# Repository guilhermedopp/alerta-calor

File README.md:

# Alerta de calor com IA para idosos

Uma caixa de baixo custo (meta: menos de R$ 60), ligada na tomada do quarto, que estima como o calor daquele cômodo está afetando o corpo de idosos e avisa o cuidador antes de o risco virar emergência, mesmo sem internet.

Projeto de Guilherme de Oliveira Pontes Pinto e Matheus Henrique Ferreira Pimentel (Sistemas de Informação, IFAL, Campus Maceió), com orientação do prof. Elvys Soares e coorientação do prof. Edison Camilo.

## O problema

- No Brasil, foram cerca de 48 mil mortes em excesso associadas ao calor entre 2000 e 2018, concentradas em idosos e em quem tem menos como se proteger (Monteiro dos Santos et al., 2024).
- Em Maceió, os dias mais quentes (máxima no percentil 95) aumentam em 5,2% as internações de idosos pelo SUS (2015–2024), mas nenhuma das 99.759 internações foi registrada como efeito do calor. Ver [`analise_maceio/`](analise_maceio/).
- O perigo está dentro de casa e das instituições de longa permanência (ILPIs), onde ninguém mede a temperatura e o idoso sente menos o calor.

## Como funciona

| Parte | O que faz | Situação |
|---|---|---|
| **Caixa** (ESP32 + sensor de temperatura e umidade) | Mede o cômodo, calcula o nível de risco e avisa com luz, som e Telegram. O alerta local funciona sem internet. Configuração pelo celular, como um roteador. | Testada em bancada |
| **IA 1: risco no corpo** (na própria caixa) | Rede neural de 2 KB que imita o modelo fisiológico JOS-3: usa as últimas 4 horas de leituras e o perfil de quem está no quarto (acamado, em repouso ou ativo) e estima o aumento da temperatura central e a perda de água por suor. | Prova de conceito pronta |
| **IA 2: assistente do cuidador** (nuvem) | Modelo de linguagem no Telegram ou WhatsApp que conhece os dados da caixa e a previsão do tempo e orienta o que fazer, sem dar diagnóstico. | Em construção |

Detalhes no [documento técnico de implementação da IA](docs/Implementacao_IA_Alerta_de_Calor.pdf) e na [proposta](docs/Proposta_AI4Good_Alerta_de_Calor.pdf).

## Resultados da IA na caixa (prova de conceito)

Teste em 8.568 momentos de simulações que a rede nunca viu, 1.188 deles com risco (aumento de pelo menos 0,2 °C na temperatura central segundo o JOS-3; limite provisório):

| Método | Alertas perdidos | Alarmes falsos |
|---|---:|---:|
| Limite fixo de índice de calor de 32 °C | 67 | 3.445 |
| Tabela com temperatura e umidade do momento | 220 | 801 |
| **IA na caixa (últimas 4 h + perfil)** | **86** | **784** |

Com quase a mesma sensibilidade do limite fixo, a IA dá **77% menos alarmes falsos**. Com o mesmo número de alarmes falsos da tabela, ela **perde 61% menos alertas**. O código em C dá o mesmo resultado que o Python (diferença máxima de 1,5 × 10⁻⁶ °C).

**Limitação importante:** a IA aprende o JOS-3, não pessoas reais. O JOS-3 tem incerteza para idosos, e os limites de risco ainda serão calibrados com dados reais.

## Estrutura do repositório

| Pasta | Conteúdo |
|---|---|
| [`firmware/`](firmware/) | Firmware de bancada (ESP32 DevKit, Etapa 11), módulo da IA (`ia_embarcada.h`, `modelo_risco.h`) e testes de bancada |
| [`ia/`](ia/) | Geração das simulações JOS-3, treino, avaliação, verificação do C, dados e figuras |
| [`assistente/`](assistente/) | Assistente do cuidador: esquema do banco, regras de segurança e perguntas de teste |
| [`caixa_3d/`](caixa_3d/) | Caixa v5 para impressão 3D em ABS (STL, scripts e instruções de impressão) |
| [`hardware/`](hardware/) | Placa de circuito no KiCad, mapa da protoboard e tutorial de montagem da bancada |
| [`analise_maceio/`](analise_maceio/) | Calor x internações de idosos em Maceió (SIH/SUS + INMET, 2015–2024) |
| [`docs/`](docs/) | Proposta e documento técnico da IA (PDF) |

## Como reproduzir

**Firmware:** ver [`firmware/README.md`](firmware/README.md).

**IA:**

```bash
cd ia
pip install -r requirements.txt
gunzip -k dados/sims.jsonl.gz                     # ou gere de novo: python gerar_simulacoes.py 400 dados/sims.jsonl
python treinar.py dados/sims.jsonl                # treina e gera modelo_risco.h
python avaliar.py 0.2 99999                       # detecção de risco e figuras
python verifica_c.py                              # compara o C com o Python
```

## Segurança e privacidade

Nenhum token, chat ID ou senha fica no código: o Wi-Fi, o bot do Telegram e o painel são configurados pela página da própria caixa e gravados na memória dela. Não versionamos dados de pessoas.

## Licença

[MIT](LICENSE).

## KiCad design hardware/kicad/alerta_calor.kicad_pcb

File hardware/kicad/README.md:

# Placa de circuito (KiCad)

Placa principal da caixa de alerta de calor, rev. 0.1, desenhada no KiCad 10.

## Resumo

| Item | Valor |
|---|---|
| Tamanho | 40 × 30 mm, 2 faces, 1,6 mm |
| Borda livre | 1,5 mm em volta (presilhas da tampa da caixa v4b) |
| Trilhas | 0,2 mm (todas, para fazer na laser do IFAL), folga de 0,3 mm |
| GND | plano de cobre nas duas faces |
| Situação | roteada; DRC sem itens desconectados |

## Peças

| Ref. | Peça | Observação |
|---|---|---|
| U1 | ESP32-C3 SuperMini | em soquete fêmea 2 × 8 (fileiras a 15,24 mm); USB-C na borda direita. Vista de cima: 5V, GND, 3V3, GPIO4…0 na fileira de baixo; GPIO5…21 na de cima |
| R1, R3 | 220 Ω | LED vermelho e azul |
| R2 | 47 Ω | LED verde (mais fraco, resistor menor; o projeto previa 56 Ω, que não veio no kit) |
| R4 | 1 kΩ | base do transistor |
| Q1 | BC337 (TO-92) | liga o buzzer |
| D1 | 1N4148 | protege o transistor |
| J2 a J6 | barras de pinos 2,54 mm | fios para os componentes da caixa |

R1–R4, Q1 e D1 ficam embaixo do ESP32, no vão do soquete. Na hora de soldar, o BC337 precisa ficar baixo, encostado na placa.

## Conectores

| Conector | Pinos (do 1 ao último) | Componente |
|---|---|---|
| J2 `AHT` | 3V3, GND, SCL, SDA | sensor AHT20 + BMP280 |
| J3 `PIR` | 3V3, OUT, GND | sensor de presença AM312 |
| J4 `LED` | R, G, B, K | LED RGB de catodo comum |
| J5 `BUZ` | +5V, − (coletor do Q1) | buzzer ativo 5 V |
| J6 `BTN` | SIG, GND | botão de silenciar |

O pino 1 de cada conector é o furo quadrado (fica embaixo em cada conector). A face de baixo da placa traz essa tabela impressa.

## Pinos do ESP32-C3

| GPIO | Uso |
|---|---|
| 3 / 4 / 5 | LED vermelho / verde / azul |
| 10 | buzzer (pelo BC337) |
| 6 / 7 | SDA / SCL do AHT20 |
| 0 | PIR |
| 1 | botão (pull-up interno) |
| 2, 8, 9 | livres (definem o modo de boot) |

## Como abrir

Abra `alerta_calor.kicad_pro` no KiCad 10. O símbolo e o footprint do ESP32-C3 SuperMini estão neste projeto (`alerta_calor.kicad_sym` e `alerta_calor.pretty/`), e as tabelas de bibliotecas já apontam para eles.

## Histórico

- 12/11/2026: a placa foi espelhada em Y. As fileiras do ESP32-C3 SuperMini estavam trocadas no footprint (conferido com a placa real). Trilhas, zonas e ligações são as mesmas, espelhadas; os conectores ficaram com o pino 1 embaixo.

## Pendências antes de fabricar

- Conferir com as peças reais a ordem dos pinos do AHT20 e do PIR, a distância entre as fileiras do ESP32 e as pernas do BC337.
- Definir se a placa será fabricada fora ou feita no IFAL. Para fazer no IFAL, trocar o footprint do Q1 por `TO-92_Inline_Wide` (o atual tem 0,22 mm entre as pernas).
- Gerar os arquivos de fabricação (Gerber e furação).

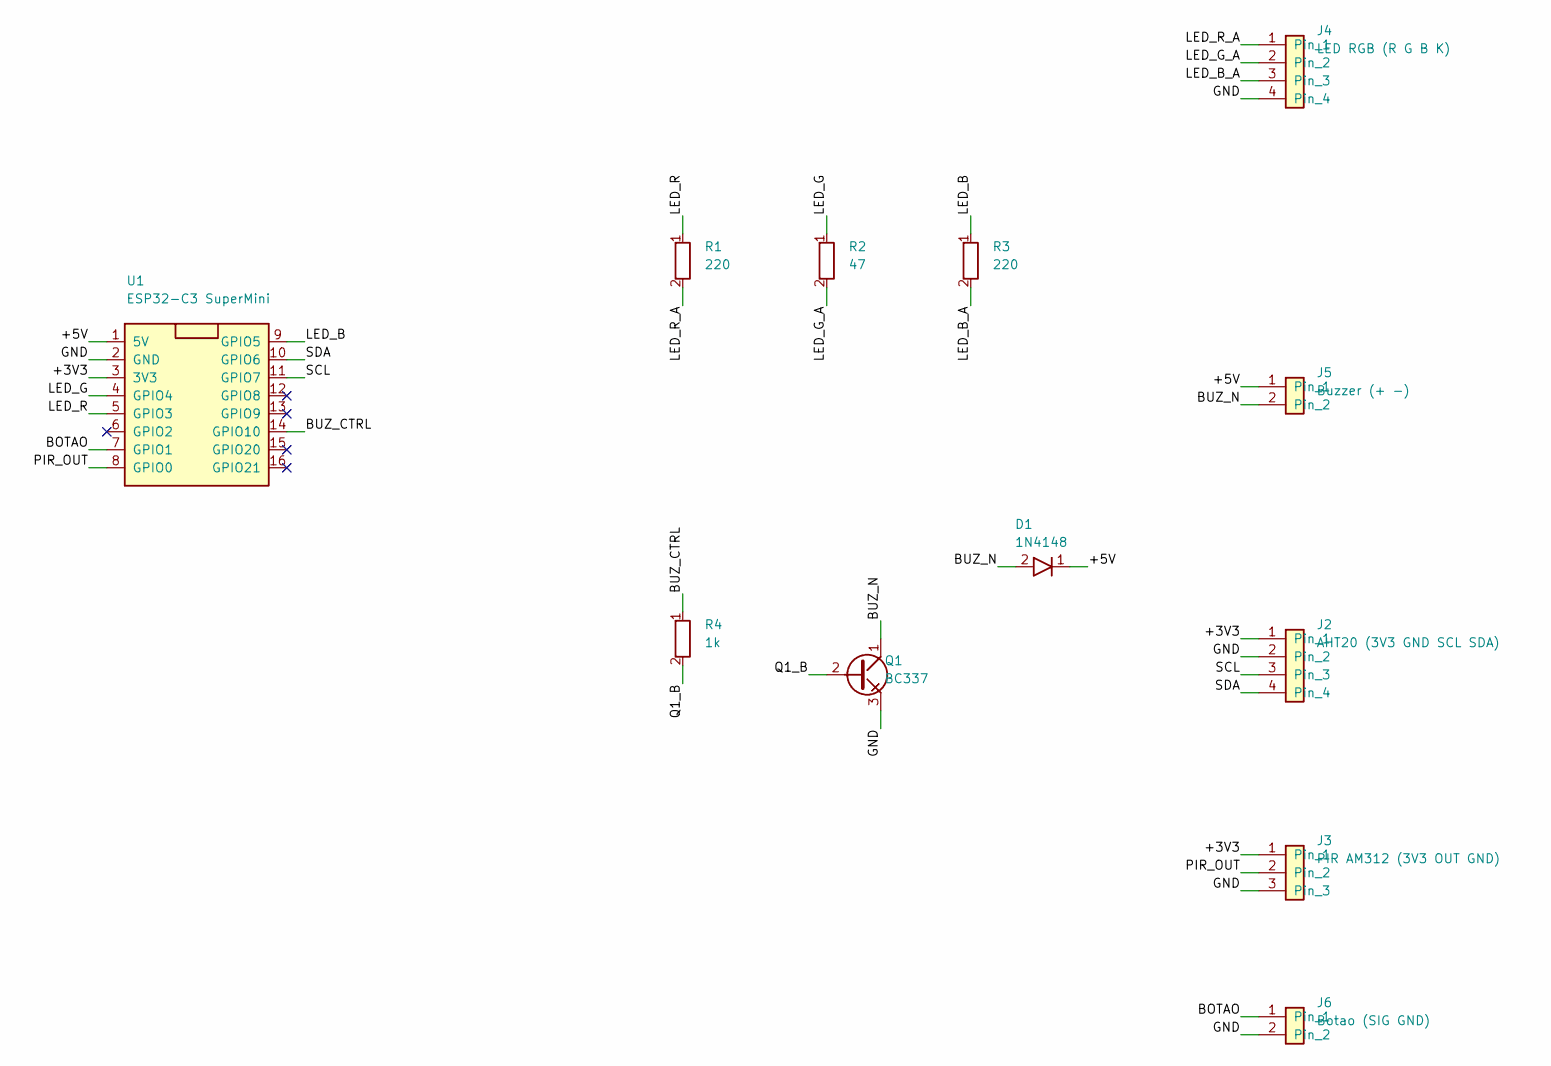
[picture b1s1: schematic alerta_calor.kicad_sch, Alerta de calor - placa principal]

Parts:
D1: 1N4148; D_DO-35_SOD27_P7.62mm_Horizontal
J2: AHT20 (3V3 GND SCL SDA); PinHeader_1x04_P2.54mm_Vertical
J3: PIR AM312 (3V3 OUT GND); PinHeader_1x03_P2.54mm_Vertical
J4: LED RGB (R G B K); PinHeader_1x04_P2.54mm_Vertical
J5: Buzzer (+ -); PinHeader_1x02_P2.54mm_Vertical
J6: Botao (SIG GND); PinHeader_1x02_P2.54mm_Vertical
Q1: BC337; TO-92_Inline
R1, R3: 220; R_Axial_DIN0207_L6.3mm_D2.5mm_P7.62mm_Horizontal
R2: 47; R_Axial_DIN0207_L6.3mm_D2.5mm_P7.62mm_Horizontal
R4: 1k; R_Axial_DIN0207_L6.3mm_D2.5mm_P7.62mm_Horizontal
U1: ESP32-C3 SuperMini; ESP32-C3_SuperMini_Soquete

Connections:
/+3V3: J2.1, J3.1, U1.3 (3V3)
/+5V: D1.1 (K), J5.1, U1.1 (5V)
/BOTAO: J6.1, U1.7 (GPIO1)
/BUZ_CTRL: R4.1, U1.14 (GPIO10)
/BUZ_N: D1.2 (A), J5.2, Q1.1 (C)
/GND: J2.2, J3.3, J4.4, J6.2, Q1.3 (E), U1.2 (GND)
/LED_B: R3.1, U1.9 (GPIO5)
/LED_B_A: J4.3, R3.2
/LED_G: R2.1, U1.4 (GPIO4)
/LED_G_A: J4.2, R2.2
/LED_R: R1.1, U1.5 (GPIO3)
/LED_R_A: J4.1, R1.2
/PIR_OUT: J3.2, U1.8 (GPIO0)
/Q1_B: Q1.2 (B), R4.2
/SCL: J2.3, U1.11 (GPIO7)
/SDA: J2.4, U1.10 (GPIO6)

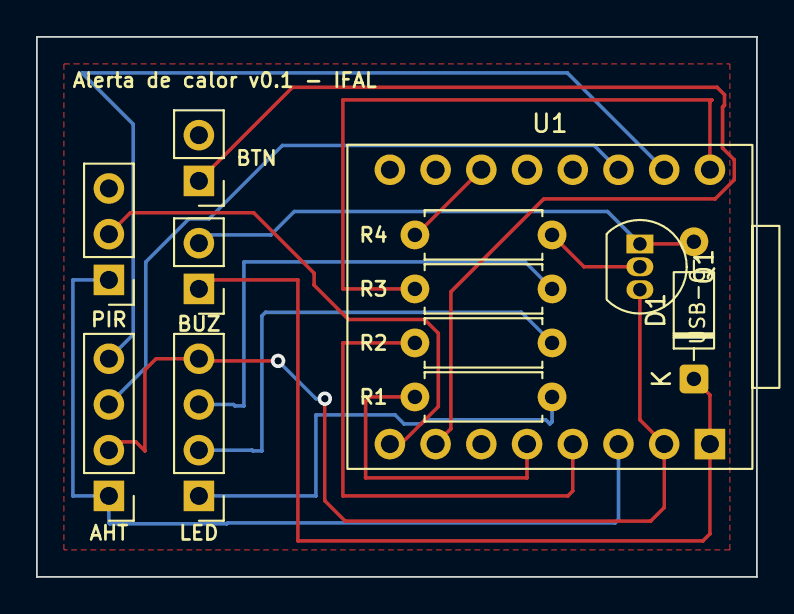
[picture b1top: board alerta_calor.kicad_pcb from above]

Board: 2 copper layers, 40.0 x 30.0 mm, 12 parts (0 on the bottom side), 16 nets.

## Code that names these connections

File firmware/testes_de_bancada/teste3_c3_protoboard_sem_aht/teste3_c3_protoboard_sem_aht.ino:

// TESTE DA PROTOBOARD DEFINITIVA, SEM O AHT20 (ESP32-C3 SuperMini)
// Testa o LED RGB, o buzzer (pelo BC337), o botão e o PIR, nessa ordem.
// O AHT20 fica para depois (ainda sem solda); este teste não usa o I2C.
//
// LIGAÇÃO (igual ao mapa "Protoboard da Caixa Definitiva")
//   GPIO3  -> R1 220 Ω -> LED vermelho
//   GPIO4  -> R2 47 Ω  -> LED verde        (catodo K do LED no GND)
//   GPIO10 -> R4 1 kΩ  -> base do BC337    (buzzer entre 5V e o coletor; diodo ainda fora)
//   GPIO1  -> botão -> GND                 (pull-up interno)
//   GPIO0  -> OUT do PIR AM312             (VCC no 3V3, GND no GND)
//
// NA ARDUINO IDE
//   Ferramentas > Placa > esp32 > "ESP32C3 Dev Module" (ou "Nologo ESP32C3 Super Mini")
//   Ferramentas > USB CDC On Boot > "Enabled"   (sem isso o Monitor Serial fica vazio)
//   Monitor Serial em 115200.
//   Se a gravação não começar: segure o botão BOOT da placa, aperte e solte RESET, solte o BOOT
//   e grave de novo. Depois de gravar, aperte RESET.

#define PINO_LED_R   3
#define PINO_LED_G   4
#define PINO_BUZZER 10
#define PINO_BOTAO   1
#define PINO_PIR     0

const unsigned long AQUECIMENTO_PIR_MS = 60000;  // o PIR precisa de ~1 min parado depois de ligar
const unsigned long PRAZO_BOTAO_MS     = 20000;  // tempo para apertar o botão
const unsigned long PRAZO_PIR_MS       = 30000;  // tempo para o PIR ver movimento depois do aquecimento

bool okLed = false, okBuzzer = false, okBotao = false, okPir = false;
unsigned long inicio;

void led(bool r, bool g) {
  digitalWrite(PINO_LED_R, r);
  digitalWrite(PINO_LED_G, g);
}

void bip(int ms) {
  digitalWrite(PINO_BUZZER, HIGH);
  delay(ms);
  digitalWrite(PINO_BUZZER, LOW);
}

// espera o usuário digitar s/n no Monitor Serial (Enter); sem resposta em 15 s conta como "n"
bool perguntar(const char* pergunta) {
  Serial.printf("%s (digite s ou n e Enter): ", pergunta);
  while (Serial.available()) Serial.read();
  unsigned long t = millis();
  while (millis() - t < 15000) {
    if (Serial.available()) {
      char c = Serial.read();
      if (c == 's' || c == 'S') { Serial.println("s"); return true; }
      if (c == 'n' || c == 'N') { Serial.println("n"); return false; }
    }
    delay(10);
  }
  Serial.println("(sem resposta)");
  return false;
}

void testeLed() {
  Serial.println("\n1) LED RGB");
  for (int i = 0; i < 3; i++) {
    Serial.println("   vermelho..."); led(1, 0); delay(1000);
    Serial.println("   verde...");    led(0, 1); delay(1000);
    Serial.println("   amarelo (os dois)..."); led(1, 1); delay(1000);
    led(0, 0); delay(400);
  }
  okLed = perguntar("   O LED acendeu vermelho, verde e amarelo?");
  if (!okLed) Serial.println("   Confira: perna K (a mais longa) no GND, R1 em i11-i14, R2 em j12-j16, fios h6->h11 e h5->h12.");
}

void testeBuzzer() {
  Serial.println("\n2) Buzzer");
  for (int i = 0; i < 3; i++) { bip(150); delay(250); }
  delay(300);
  bip(800);
  okBuzzer = perguntar("   Ouviu 3 bips curtos e 1 longo?");
  if (!okBuzzer) Serial.println("   Confira: BC337 em d20 d21 d22 (E B C, lado reto para a coluna a), a20 no GND, buzzer + em a27 e d27 no 5V, fio c22->d24.");
}

void testeBotao() {
  Serial.println("\n3) Botao: aperte o botao agora (20 s)");
  unsigned long t = millis();
  int apertos = 0;
  bool anterior = HIGH;
  while (millis() - t < PRAZO_BOTAO_MS && apertos < 3) {
    bool agora = digitalRead(PINO_BOTAO);
    if (anterior == HIGH && agora == LOW) {
      apertos++;
      Serial.printf("   apertou (%d de 3)\n", apertos);
      led(0, 1); bip(60);
    }
    if (agora == HIGH) led(0, 0);
    anterior = agora;
    delay(30);   // filtra o repique do contato
  }
  led(0, 0);
  okBotao = apertos > 0;
  if (apertos == 0) Serial.println("   Nenhum aperto. Confira: perna A em i8, a perna na diagonal no trilho - (GND).");
  else if (apertos < 3) Serial.println("   Funcionou (aperte 3 vezes da proxima vez para conferir melhor).");
  else Serial.println("   OK.");
}

void testePir() {
  Serial.println("\n4) PIR: fique parado longe do sensor durante o aquecimento");
  while (millis() - inicio < AQUECIMENTO_PIR_MS) {
    unsigned long falta = (AQUECIMENTO_PIR_MS - (millis() - inicio)) / 1000;
    Serial.printf("   aquecendo... %lu s\n", falta);
    delay(5000);
  }
  Serial.println("   Pronto. Passe a mao na frente do PIR (30 s).");
  unsigned long t = millis();
  int deteccoes = 0;
  bool anterior = digitalRead(PINO_PIR);
  while (millis() - t < PRAZO_PIR_MS && deteccoes < 2) {
    bool agora = digitalRead(PINO_PIR);
    led(agora, 0);
    if (!anterior && agora) { deteccoes++; Serial.printf("   movimento detectado (%d)\n", deteccoes); }
    if (anterior && !agora) Serial.println("   parou");
    anterior = agora;
    delay(50);
  }
  led(0, 0);
  okPir = deteccoes > 0;
  if (!okPir) Serial.println("   Nada detectado. Confira a ordem VCC/OUT/GND embaixo do PIR, i4->j22 (3V3), h9->h23 e j24 no GND.");
}

void setup() {
  // buzzer e LED desligados antes de tudo
  pinMode(PINO_BUZZER, OUTPUT); digitalWrite(PINO_BUZZER, LOW);
  pinMode(PINO_LED_R, OUTPUT);
  pinMode(PINO_LED_G, OUTPUT);
  led(0, 0);
  pinMode(PINO_BOTAO, INPUT_PULLUP);
  pinMode(PINO_PIR, INPUT);
  inicio = millis();

  Serial.begin(115200);
  delay(2500);   // tempo para o Monitor Serial conectar pela USB
  Serial.println("\n=== Teste da protoboard (ESP32-C3, sem AHT20) ===");

  testeLed();
  testeBuzzer();
  testeBotao();
  testePir();

  Serial.println("\n=== RESULTADO ===");
  Serial.printf("LED RGB : %s\n", okLed    ? "OK" : "FALHOU");
  Serial.printf("Buzzer  : %s\n", okBuzzer ? "OK" : "FALHOU");
  Serial.printf("Botao   : %s\n", okBotao  ? "OK" : "FALHOU");
  Serial.printf("PIR     : %s\n", okPir    ? "OK" : "FALHOU");
  Serial.println("AHT20   : nao testado (sem solda)");
  Serial.println("\nModo livre: PIR acende o vermelho, botao acende o verde e bipa. Aperte RESET para repetir.");
}

void loop() {
  // modo livre, para ficar testando a vontade
  static bool botaoAnterior = HIGH;
  bool botao = digitalRead(PINO_BOTAO);
  bool pir = digitalRead(PINO_PIR);
  led(pir, botao == LOW);
  if (botaoAnterior == HIGH && botao == LOW) bip(80);
  botaoAnterior = botao;
  delay(30);
}
